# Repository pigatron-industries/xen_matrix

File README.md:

# Matrix Mixer

A Eurorack module 6x6 matrix mixer

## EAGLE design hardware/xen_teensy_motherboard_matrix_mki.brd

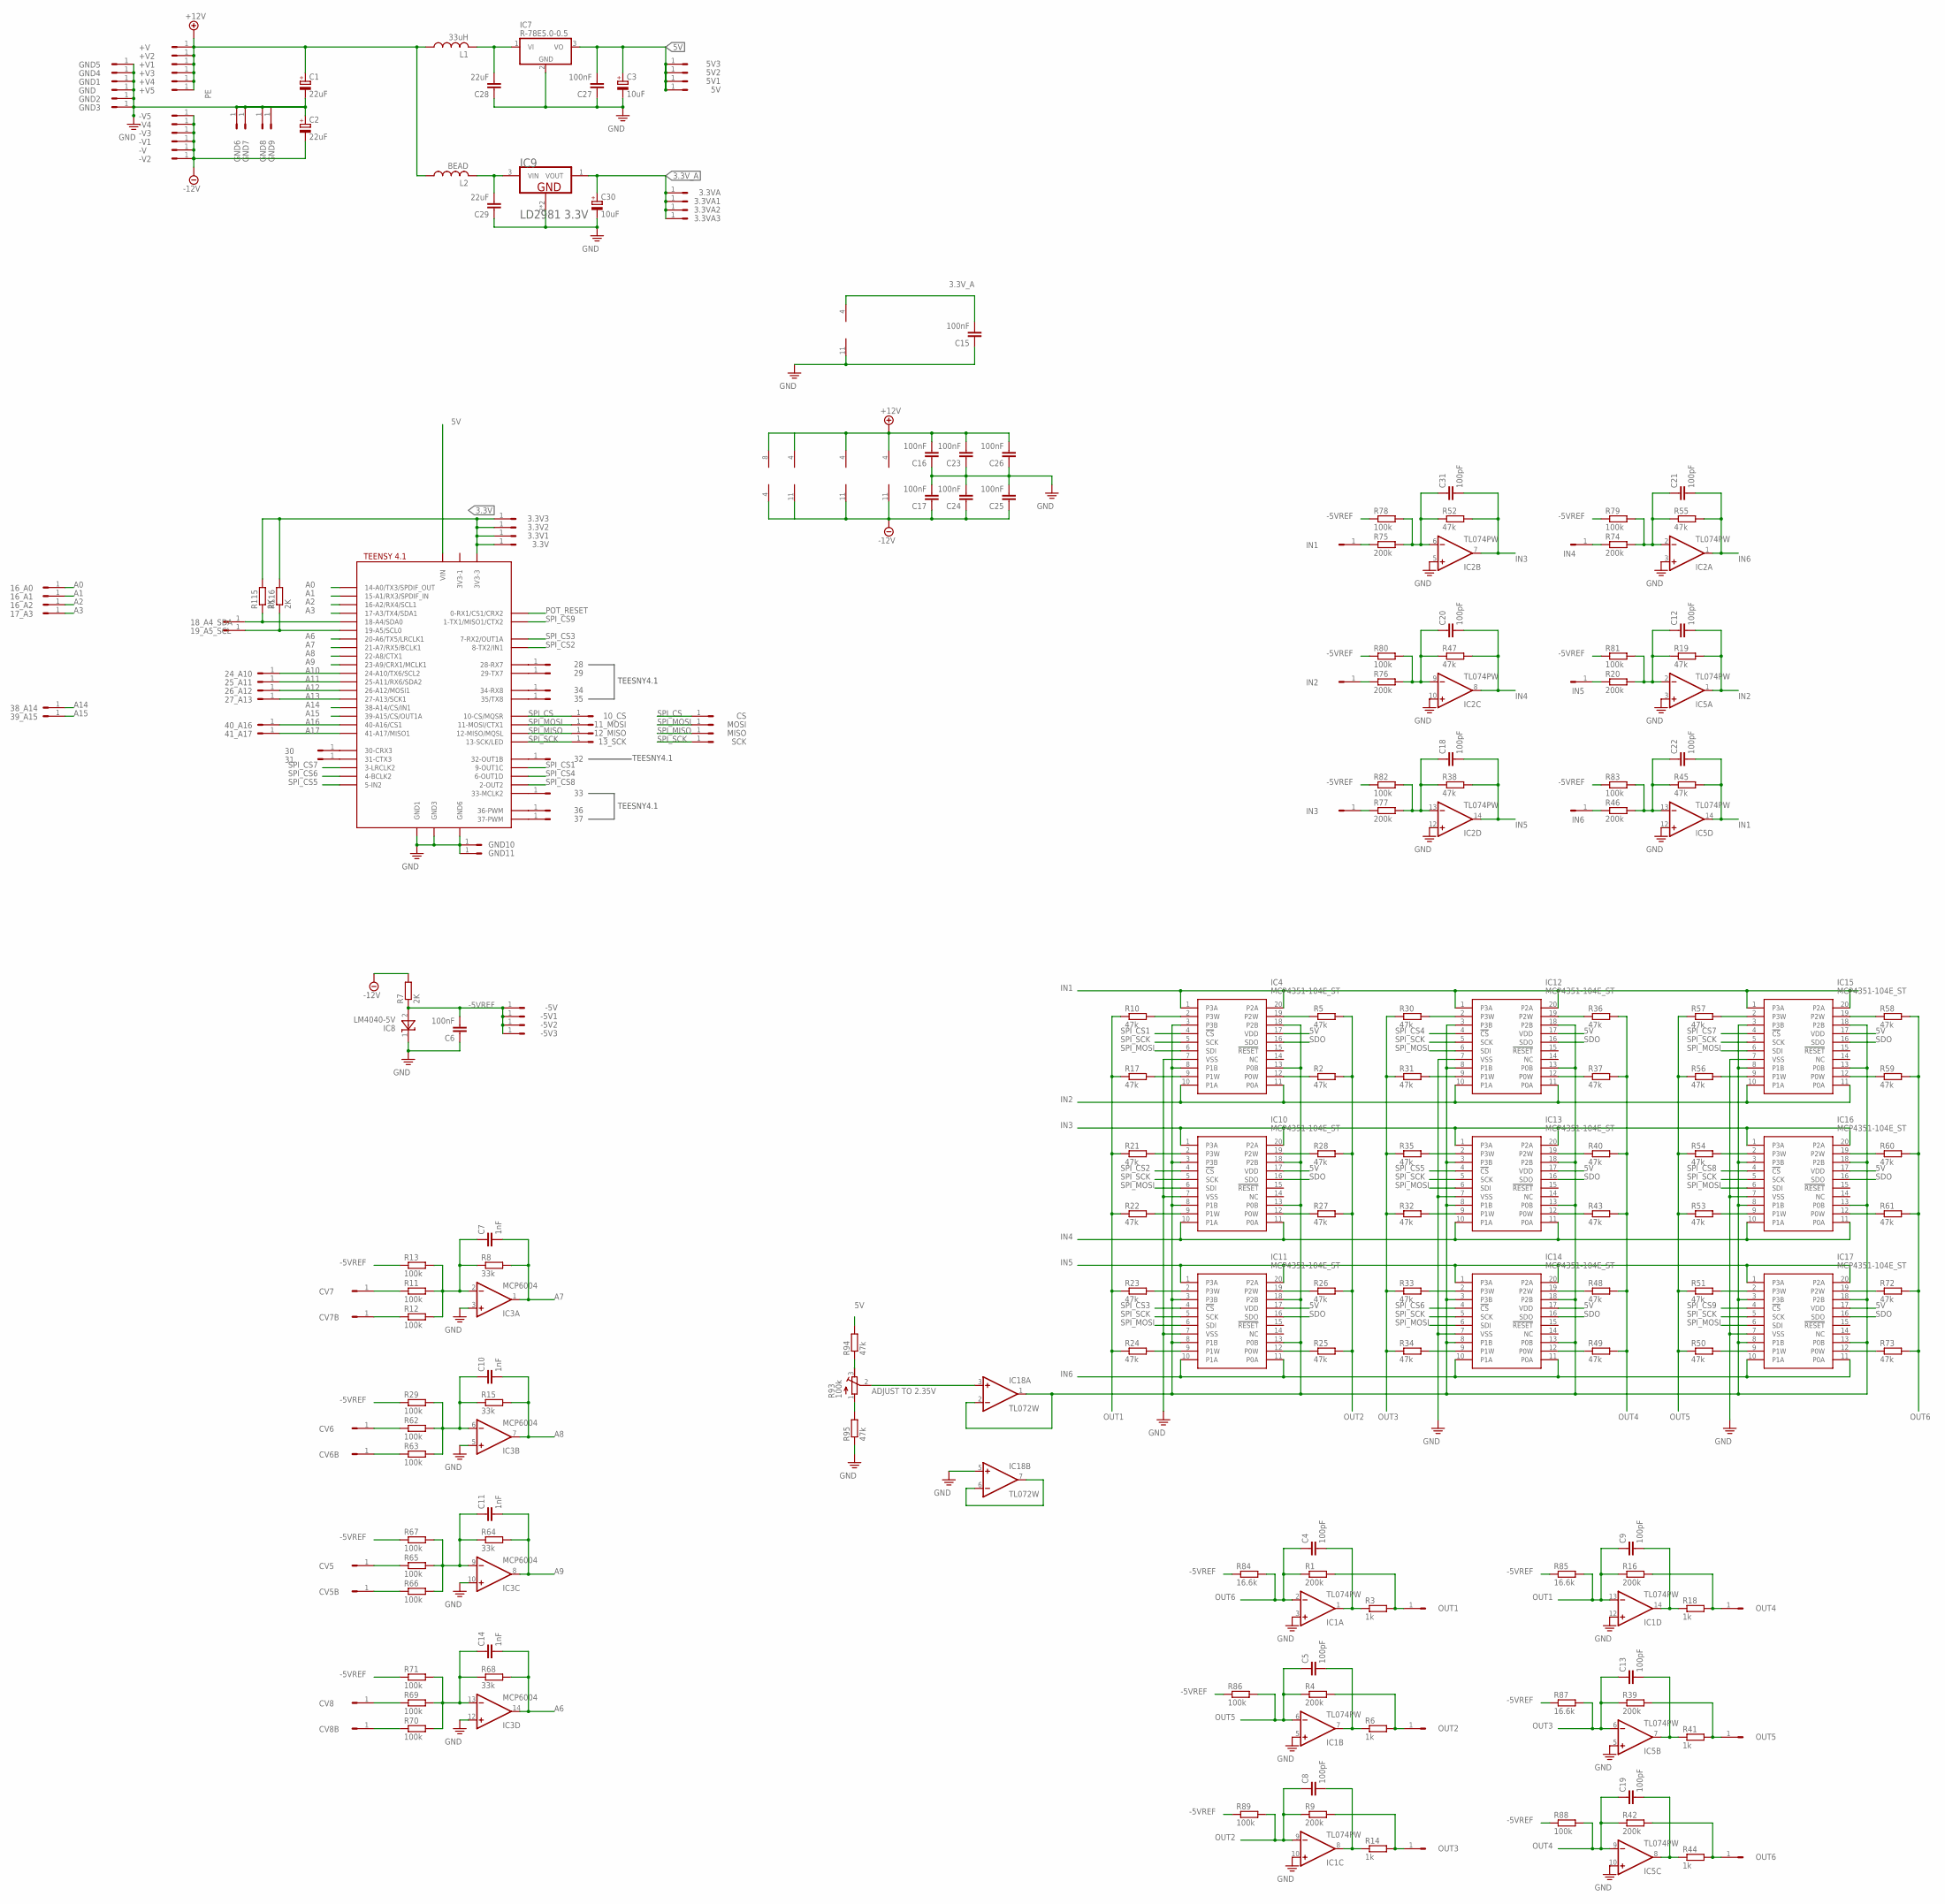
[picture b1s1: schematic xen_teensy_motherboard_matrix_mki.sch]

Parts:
3.3V, 3.3V1, 3.3V2, 3.3V3, 3.3VA, 3.3VA1, 3.3VA2, 3.3VA3, 5V, 5V1, 5V2, 5V3, 10_CS, 11_MOSI, 12_MISO, 13_SCK, 16_A0, 16_A1, 16_A2, 17_A3, 18_A4_SDA, 19_A5_SCL, 24_A10, 25_A11, 26_A12, 27_A13, 28, 29, 30, 31, 32, 33, 34, 35, 36, 37, 38_A14, 39_A15, 40_A16, 41_A17: HEADER/MALE/01
+V, +V1, +V2, +V3, +V4, +V5: HEADER/MALE/01
-5V, -5V1, -5V2, -5V3: HEADER/MALE/01
-V, -V1, -V2, -V3, -V4, -V5: HEADER/MALE/01
C1, C2: 22uF; SV-C
C3, C30: 10uF; SV-B
C4, C5, C8, C9, C12, C13, C18, C19, C20, C21, C22, C31: 100pF; C0603
C6, C15, C16, C17, C23, C24, C25, C26, C27: 100nF; C0603
C7, C10, C11, C14: 1nF; C0603
C28, C29: 22uF; C0805
CS: HEADER/MALE/01
CV5, CV5B, CV6, CV6B, CV7, CV7B, CV8, CV8B: HEADER/MALE/01
GND, GND1, GND2, GND3, GND4, GND5, GND6, GND7, GND8, GND9, GND10, GND11: HEADER/MALE/01
IC1, IC2, IC5: TL074PW; TSSOP14
IC3: MCP6004; TSSOP14
IC4, IC10, IC11, IC12, IC13, IC14, IC15, IC16, IC17: MCP4351-104E_ST; SOP65P640X120-20N
IC6: TEENSY41-OUTER; TENNSY41-OUTER
IC7: R-78E5.0-0.5; WE78
IC8: LM4040-5V; SOT-23
IC9: LD2981 3.3V; LD2981-SOT89
IC18: TL072W; TSSOP08
IN1, IN2, IN3, IN4, IN5, IN6: HEADER/MALE/01
L1: 33uH; L2012C
L2: BEAD; R0603
MISO: HEADER/MALE/01
MOSI: HEADER/MALE/01
OUT1, OUT2, OUT3, OUT4, OUT5, OUT6: HEADER/MALE/01
R1, R4, R9, R16, R20, R39, R42, R46, R74, R75, R76, R77: 200k; R0603
R2, R5, R10, R17, R19, R21, R22, R23, R24, R25, R26, R27, R28, R30, R31, R32, R33, R34, R35, R36, R37, R38, R40, R43, R45, R47, R48, R49, R50, R51, R52, R53, R54, R55, R56, R57, R58, R59, R60, R61, R72, R73, R94, R95: 47k; R0603
R3, R6, R14, R18, R41, R44: 1k; R0603
R7, R115, R116: 2K; R0603
R8, R15, R64, R68: 33k; R0603
R11, R12, R13, R29, R62, R63, R65, R66, R67, R69, R70, R71, R78, R79, R80, R81, R82, R83, R86, R88, R89: 100k; R0603
R84, R85, R87: 16.6k; R0603
R93: 100k; TRIMMER/64B
SCK: HEADER/MALE/01

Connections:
3.3V: 3.3V.1, 3.3V1.1, 3.3V2.1, 3.3V3.1, IC6.3V3-3, R115.2, R116.2
3.3V_A: 3.3VA.1, 3.3VA1.1, 3.3VA2.1, 3.3VA3.1, C15.2, C30.+, IC3.4 (V+), IC9.1 (VOUT)
5V: 5V.1, 5V1.1, 5V2.1, 5V3.1, C3.+, C27.2, IC4.17 (VDD), IC6.VIN, IC7.3 (VO), IC10.17 (VDD), IC11.17 (VDD), IC12.17 (VDD), IC13.17 (VDD), IC14.17 (VDD), IC15.17 (VDD), IC16.17 (VDD), IC17.17 (VDD), R94.2
+12V: +V.1, +V1.1, +V2.1, +V3.1, +V4.1, +V5.1, C1.+, C16.2, C23.2, C26.2, IC1.4 (V+), IC2.4 (V+), IC5.4 (V+), IC18.8 (V+), L1.1, L2.1
-5VREF: -5V.1, -5V1.1, -5V2.1, -5V3.1, C6.2, IC8.2 (A), R7.1, R13.1, R29.1, R67.1, R71.1, R78.1, R79.1, R80.1, R81.1, R82.1, R83.1, R84.1, R85.1, R86.1, R87.1, R88.1, R89.1
-12V: -V.1, -V1.1, -V2.1, -V3.1, -V4.1, -V5.1, C2.-, C17.1, C24.1, C25.1, IC1.11 (V-), IC2.11 (V-), IC5.11 (V-), IC18.4 (V-), R7.2
A0: 16_A0.1, IC6.14-A0/TX3/SPDIF_OUT
A1: 16_A1.1, IC6.15-A1/RX3/SPDIF_IN
A2: 16_A2.1, IC6.16-A2/RX4/SCL1
A3: 17_A3.1, IC6.17-A3/TX4/SDA1
A5: 19_A5_SCL.1, IC6.19-A5/SCL0, R116.1
A6: C14.2, IC3.14 (OUT), IC6.20-A6/TX5/LRCLK1, R68.2
A7: C7.2, IC3.1 (OUT), IC6.21-A7/RX5/BCLK1, R8.2
A8: C10.2, IC3.7 (OUT), IC6.22-A8/CTX1, R15.2
A9: C11.2, IC3.8 (OUT), IC6.23-A9/CRX1/MCLK1, R64.2
A10: 24_A10.1, IC6.24-A10/TX6/SCL2
A11: 25_A11.1, IC6.25-A11/RX6/SDA2
A12: 26_A12.1, IC6.26-A12/MOSI1
A13: 27_A13.1, IC6.27-A13/SCK1
A14: 38_A14.1, IC6.38-A14/CS/IN1
A15: 39_A15.1, IC6.39-A15/CS/OUT1A
A16: 40_A16.1, IC6.40-A16/CS1
A17: 41_A17.1, IC6.41-A17/MISO1
DAC1: IN6.1, R46.1
DAC2: IN5.1, R20.1
IN1: C22.2, IC4.1 (P3A), IC4.20 (P2A), IC5.14 (OUT), IC12.1 (P3A), IC12.20 (P2A), IC15.1 (P3A), IC15.20 (P2A), R45.2
IN2: C12.2, IC4.10 (P1A), IC4.11 (P0A), IC5.1 (OUT), IC12.10 (P1A), IC12.11 (P0A), IC15.10 (P1A), IC15.11 (P0A), R19.2
IN3: C31.2, IC2.7 (OUT), IC10.1 (P3A), IC10.20 (P2A), IC13.1 (P3A), IC13.20 (P2A), IC16.1 (P3A), IC16.20 (P2A), R52.2
IN4: C20.2, IC2.8 (OUT), IC10.10 (P1A), IC10.11 (P0A), IC13.10 (P1A), IC13.11 (P0A), IC16.10 (P1A), IC16.11 (P0A), R47.2
IN5: C18.2, IC2.14 (OUT), IC11.1 (P3A), IC11.20 (P2A), IC14.1 (P3A), IC14.20 (P2A), IC17.1 (P3A), IC17.20 (P2A), R38.2
IN6: C21.2, IC2.1 (OUT), IC11.10 (P1A), IC11.11 (P0A), IC14.10 (P1A), IC14.11 (P0A), IC17.10 (P1A), IC17.11 (P0A), R55.2
unnamed: IC4.2 (P3W), R10.2
unnamed: C18.1, IC2.13 (-IN), R38.1, R77.2, R82.2
unnamed: C4.2, IC1.1 (OUT), R3.1
unnamed: OUT1.1, R1.2, R3.2
unnamed: IC4.3 (P3B), IC4.8 (P1B), IC4.13 (P0B), IC4.18 (P2B), IC10.3 (P3B), IC10.8 (P1B), IC10.13 (P0B), IC10.18 (P2B), IC11.3 (P3B), IC11.8 (P1B), IC11.13 (P0B), IC11.18 (P2B), IC12.3 (P3B), IC12.8 (P1B), IC12.13 (P0B), IC12.18 (P2B), IC13.3 (P3B), IC13.8 (P1B), IC13.13 (P0B), IC13.18 (P2B), IC14.3 (P3B), IC14.8 (P1B), IC14.13 (P0B), IC14.18 (P2B), IC15.3 (P3B), IC15.8 (P1B), IC15.13 (P0B), IC15.18 (P2B), IC16.3 (P3B), IC16.8 (P1B), IC16.13 (P0B), IC16.18 (P2B), IC17.3 (P3B), IC17.8 (P1B), IC17.13 (P0B), IC17.18 (P2B), IC18.1 (OUT), IC18.2 (-IN)
unnamed: C5.2, IC1.7 (OUT), R6.1
unnamed: OUT2.1, R4.2, R6.2
unnamed: C7.1, IC3.2 (-IN), R8.1, R11.2, R12.2, R13.2
unnamed: IC18.3 (+IN), R93.2 (S)
unnamed: C8.2, IC1.8 (OUT), R14.1
unnamed: OUT3.1, R9.2, R14.2
unnamed: C20.1, IC2.9 (-IN), R47.1, R76.2, R80.2
unnamed: CV7B.1, R12.1
unnamed: CV7.1, R11.1
unnamed: C9.2, IC1.14 (OUT), R18.1
unnamed: C10.1, IC3.6 (-IN), R15.1, R29.2, R62.2, R63.2
unnamed: OUT4.1, R16.2, R18.2
unnamed: CV6.1, R62.1
unnamed: CV6B.1, R63.1
unnamed: C12.1, IC5.2 (-IN), R19.1, R20.2, R81.2
unnamed: IC18.6 (-IN), IC18.7 (OUT)
unnamed: IC4.9 (P1W), R17.2
unnamed: IC10.2 (P3W), R21.2
unnamed: IC10.9 (P1W), R22.2
unnamed: IC11.2 (P3W), R23.2
unnamed: IC11.9 (P1W), R24.2
unnamed: C31.1, IC2.6 (-IN), R52.1, R75.2, R78.2
unnamed: IC11.12 (P0W), R25.1
unnamed: IC11.19 (P2W), R26.1
unnamed: IC10.12 (P0W), R27.1
unnamed: IC10.19 (P2W), R28.1
unnamed: C13.2, IC5.7 (OUT), R41.1
unnamed: IC4.12 (P0W), R2.1
unnamed: IC4.19 (P2W), R5.1
unnamed: IC12.2 (P3W), R30.2
unnamed: IC12.9 (P1W), R31.2
unnamed: IC13.2 (P3W), R35.2
unnamed: IC13.9 (P1W), R32.2
unnamed: IC14.2 (P3W), R33.2
unnamed: IC14.9 (P1W), R34.2
unnamed: OUT5.1, R39.2, R41.2
unnamed: R93.1 (E), R95.2
unnamed: C19.2, IC5.8 (OUT), R44.1
unnamed: 18_A4_SDA.1, IC6.18-A4/SDA0, R115.1
unnamed: IC14.12 (P0W), R49.1
unnamed: OUT6.1, R42.2, R44.2
unnamed: C22.1, IC5.13 (-IN), R45.1, R46.2, R83.2
unnamed: R93.3 (A), R94.1
unnamed: C21.1, IC2.2 (-IN), R55.1, R74.2, R79.2
unnamed: C28.2, IC7.1 (VI), L1.2
unnamed: IC14.19 (P2W), R48.1
unnamed: IC13.12 (P0W), R43.1
unnamed: IC13.19 (P2W), R40.1
unnamed: IC12.12 (P0W), R37.1
unnamed: IC12.19 (P2W), R36.1
unnamed: C14.1, IC3.13 (-IN), R68.1, R69.2, R70.2, R71.2
unnamed: IC15.2 (P3W), R57.2
unnamed: IC15.9 (P1W), R56.2
unnamed: CV8.1, R69.1
unnamed: IC16.2 (P3W), R54.2
unnamed: IC16.9 (P1W), R53.2
unnamed: IC17.2 (P3W), R51.2
unnamed: IC17.9 (P1W), R50.2
unnamed: IC17.12 (P0W), R73.1
unnamed: IC17.19 (P2W), R72.1
unnamed: IC16.12 (P0W), R61.1
unnamed: CV8B.1, R70.1
unnamed: CV5B.1, R66.1
unnamed: CV5.1, R65.1
unnamed: C11.1, IC3.9 (-IN), R64.1, R65.2, R66.2, R67.2
unnamed: C29.2, IC9.3 (VIN), L2.2
unnamed: IC16.19 (P2W), R60.1
unnamed: IC15.12 (P0W), R59.1
unnamed: IC15.19 (P2W), R58.1
unnamed: IN1.1, R75.1
unnamed: IN2.1, R76.1
unnamed: IN3.1, R77.1
unnamed: IN4.1, R74.1
unnamed: 28.1, IC6.28-RX7
unnamed: 29.1, IC6.29-TX7
unnamed: 30.1, IC6.30-CRX3
unnamed: 31.1, IC6.31-CTX3
unnamed: 32.1, IC6.32-OUT1B
unnamed: 34.1, IC6.34-RX8
unnamed: 35.1, IC6.35-TX8 (35/TX8)
unnamed: 33.1, IC6.33-MCLK2
unnamed: 36.1, IC6.36-PWM
unnamed: 37.1, IC6.37-PWM
OUT1: C9.1, IC1.13 (-IN), R10.1, R16.1, R17.1, R21.1, R22.1, R23.1, R24.1, R85.2
OUT2: C8.1, IC1.9 (-IN), R2.2, R5.2, R9.1, R25.2, R26.2, R27.2, R28.2, R89.2
OUT3: C13.1, IC5.6 (-IN), R30.1, R31.1, R32.1, R33.1, R34.1, R35.1, R39.1, R87.2
OUT4: C19.1, IC5.9 (-IN), R36.2, R37.2, R40.2, R42.1, R43.2, R48.2, R49.2, R88.2
OUT5: C5.1, IC1.6 (-IN), R4.1, R50.1, R51.1, R53.1, R54.1, R56.1, R57.1, R86.2
OUT6: C4.1, IC1.2 (-IN), R1.1, R58.2, R59.2, R60.2, R61.2, R72.2, R73.2, R84.2
PE: C1.-, C2.+, C3.-, C6.1, C15.1, C16.1, C17.2, C23.1, C24.2, C25.2, C26.1, C27.1, C28.1, C29.1, C30.-, GND.1, GND1.1, GND2.1, GND3.1, GND4.1, GND5.1, GND6.1, GND7.1, GND8.1, GND9.1, GND10.1, GND11.1, IC1.3 (+IN), IC1.5 (+IN), IC1.10 (+IN), IC1.12 (+IN), IC2.3 (+IN), IC2.5 (+IN), IC2.10 (+IN), IC2.12 (+IN), IC3.3 (+IN), IC3.5 (+IN), IC3.10 (+IN), IC3.11 (V-), IC3.12 (+IN), IC4.7 (VSS), IC5.3 (+IN), IC5.5 (+IN), IC5.10 (+IN), IC5.12 (+IN), IC6.GND1, IC6.GND3, IC6.GND6, IC7.2 (GND), IC8.1 (C), IC9.2 (GND), IC9.2-2 (GND), IC10.7 (VSS), IC11.7 (VSS), IC12.7 (VSS), IC13.7 (VSS), IC14.7 (VSS), IC15.7 (VSS), IC16.7 (VSS), IC17.7 (VSS), IC18.5 (+IN), R95.1
POT_RESET: IC6.0-RX1/CS1/CRX2
SDO: IC4.16 (SDO), IC10.16 (SDO), IC11.16 (SDO), IC12.16 (SDO), IC13.16 (SDO), IC14.16 (SDO), IC15.16 (SDO), IC16.16 (SDO), IC17.16 (SDO)
SPI_CS: 10_CS.1, CS.1, IC6.10-CS\MQSR (10-CS/MQSR)
SPI_CS1: IC4.4 (!CS), IC6.9-OUT1C
SPI_CS2: IC6.8-TX2/IN1, IC10.4 (!CS)
SPI_CS3: IC6.7-RX2/OUT1A, IC11.4 (!CS)
SPI_CS4: IC6.6-OUT1D, IC12.4 (!CS)
SPI_CS5: IC6.5-IN2, IC13.4 (!CS)
SPI_CS6: IC6.4-BCLK2, IC14.4 (!CS)
SPI_CS7: IC6.3-LRCLK2, IC15.4 (!CS)
SPI_CS8: IC6.2-OUT2, IC16.4 (!CS)
SPI_CS9: IC6.1-TX1/MISO1/CTX2, IC17.4 (!CS)
SPI_MISO: 12_MISO.1, IC6.12-MISO/MQSL, MISO.1
SPI_MOSI: 11_MOSI.1, IC4.6 (SDI), IC6.11-MOSI/CTX1, IC10.6 (SDI), IC11.6 (SDI), IC12.6 (SDI), IC13.6 (SDI), IC14.6 (SDI), IC15.6 (SDI), IC16.6 (SDI), IC17.6 (SDI), MOSI.1
SPI_SCK: 13_SCK.1, IC4.5 (SCK), IC6.13-SCK/LED, IC10.5 (SCK), IC11.5 (SCK), IC12.5 (SCK), IC13.5 (SCK), IC14.5 (SCK), IC15.5 (SCK), IC16.5 (SCK), IC17.5 (SCK), SCK.1

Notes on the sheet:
TEESNY4.1
ADJUST TO 2.35V

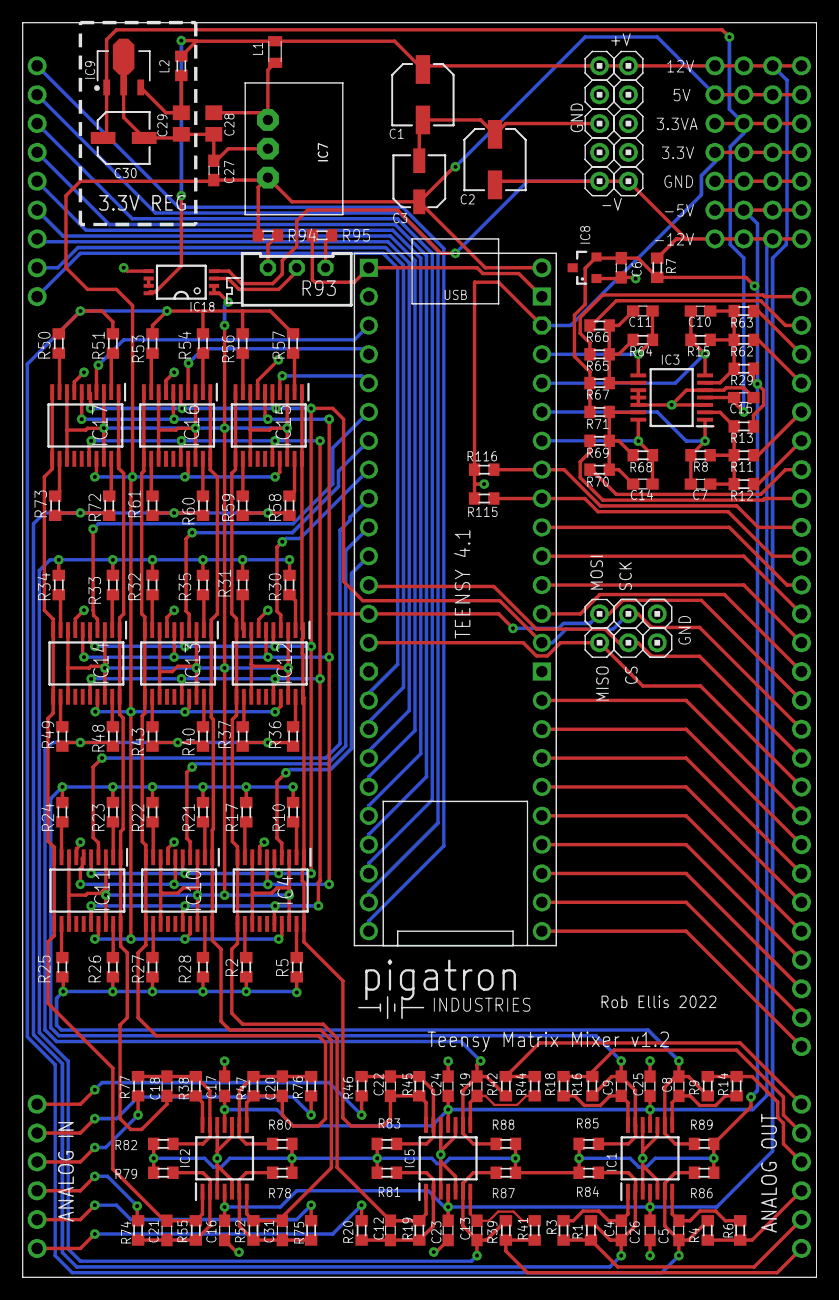
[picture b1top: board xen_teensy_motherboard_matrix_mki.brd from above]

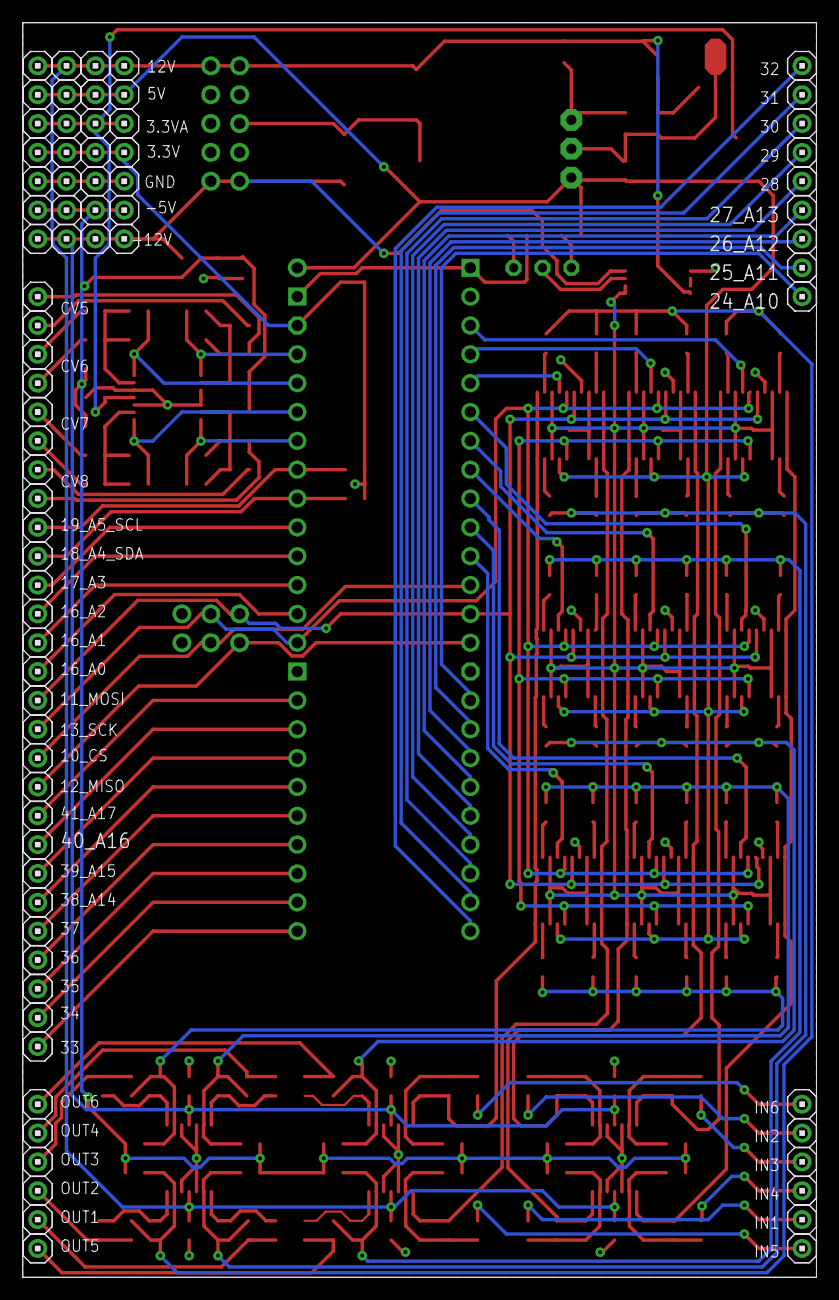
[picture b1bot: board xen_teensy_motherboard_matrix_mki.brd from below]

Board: 2 copper layers, 69.9 x 110.5 mm, 238 parts (76 on the bottom side), 140 nets.

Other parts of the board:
U$1: PIGATRON-LOGO

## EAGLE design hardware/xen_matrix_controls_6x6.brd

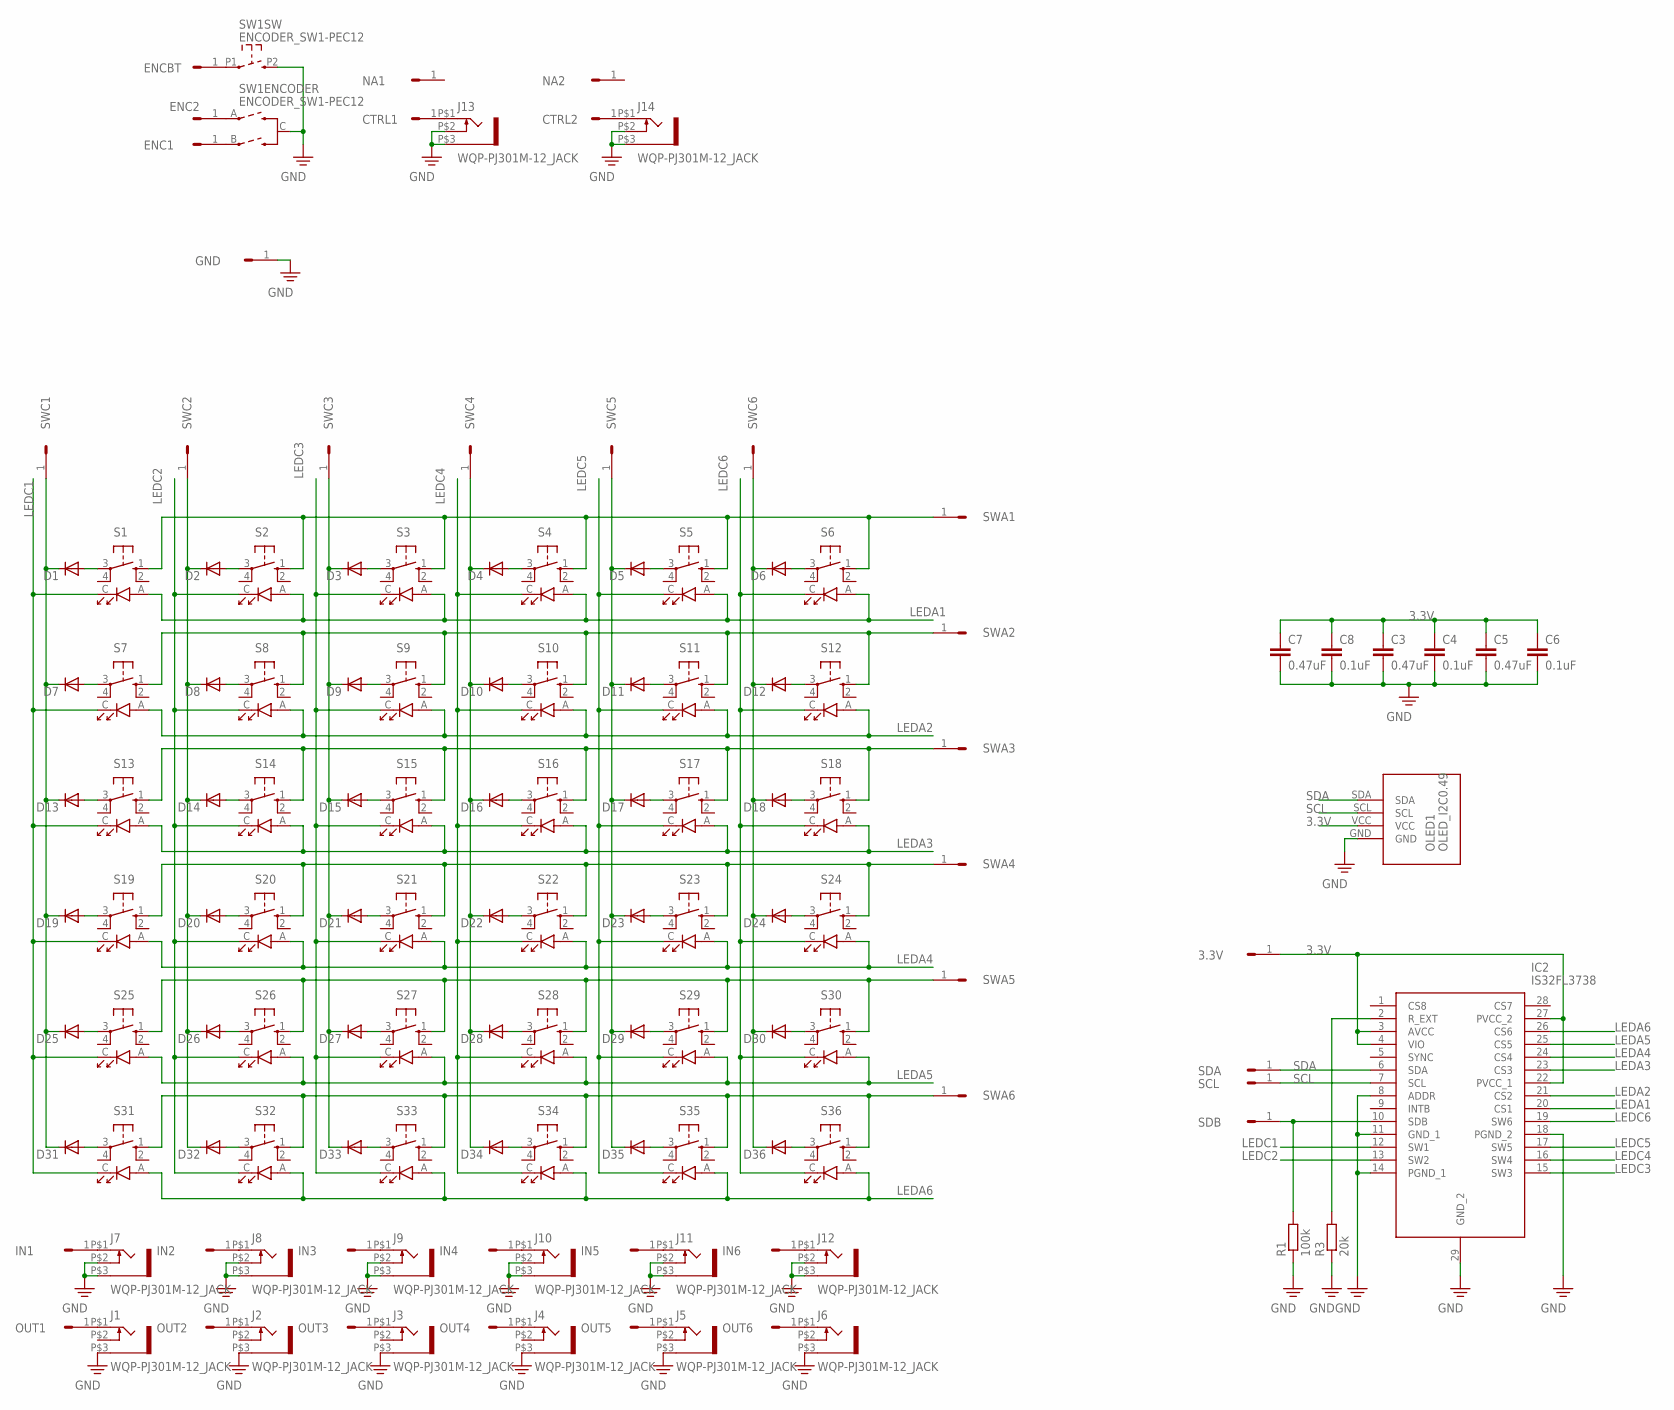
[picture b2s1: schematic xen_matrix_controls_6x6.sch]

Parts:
3.3V: HEADER/MALE/01
C3, C5, C7: 0.47uF; C0603
C4, C6, C8: 0.1uF; C0603
CTRL1, CTRL2: HEADER/MALE/01
D1, D2, D3, D4, D5, D6, D7, D8, D9, D10, D11, D12, D13, D14, D15, D16, D17, D18, D19, D20, D21, D22, D23, D24, D25, D26, D27, D28, D29, D30, D31, D32, D33, D34, D35, D36: 1N4148SOD-123; SOD-123
ENC1, ENC2: HEADER/MALE/01
ENCBT: HEADER/MALE/01
GND: HEADER/MALE/01
IC2: IS32FL3738; TSSOP29
IN1, IN2, IN3, IN4, IN5, IN6: HEADER/MALE/01
J1, J2, J3, J4, J5, J6, J7, J8, J9, J10, J11, J12, J13, J14: WQP-PJ301M-12_JACK
NA1, NA2: HEADER/MALE/01
OLED1: OLED_I2C0.49; OLEDM0.49
OUT1, OUT2, OUT3, OUT4, OUT5, OUT6: HEADER/MALE/01
R1: 100k; R0603
R3: 20k; R0603
S1, S2, S3, S4, S5, S6, S7, S8, S9, S10, S11, S12, S13, S14, S15, S16, S17, S18, S19, S20, S21, S22, S23, S24, S25, S26, S27, S28, S29, S30, S31, S32, S33, S34, S35, S36: SW-LEDTHONK; SW-PUSH-TACT-LED-THONK
SCL: HEADER/MALE/01
SDA: HEADER/MALE/01
SDB: HEADER/MALE/01
SW1: ENCODER_SW1-PEC12; PEC12_INCREMENTAL_ENCODER
SWA1, SWA2, SWA3, SWA4, SWA5, SWA6: HEADER/MALE/01
SWC1, SWC2, SWC3, SWC4, SWC5, SWC6: HEADER/MALE/01

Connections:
3.3V: 3.3V.1, C3.1, C4.1, C5.1, C6.1, C7.1, C8.1, IC2.3 (AVCC), IC2.4 (VIO), IC2.22 (PVCC_1), IC2.27 (PVCC_2), OLED1.VCC
LEDA1: IC2.20 (CS1), S1.A, S2.A, S3.A, S4.A, S5.A, S6.A
LEDA2: IC2.21 (CS2), S7.A, S8.A, S9.A, S10.A, S11.A, S12.A
LEDA3: IC2.23 (CS3), S13.A, S14.A, S15.A, S16.A, S17.A, S18.A
LEDA4: IC2.24 (CS4), S19.A, S20.A, S21.A, S22.A, S23.A, S24.A
LEDA5: IC2.25 (CS5), S25.A, S26.A, S27.A, S28.A, S29.A, S30.A
LEDA6: IC2.26 (CS6), S31.A, S32.A, S33.A, S34.A, S35.A, S36.A
LEDC1: IC2.12 (SW1), S1.C, S7.C, S13.C, S19.C, S25.C, S31.C
LEDC2: IC2.13 (SW2), S2.C, S8.C, S14.C, S20.C, S26.C, S32.C
LEDC3: IC2.15 (SW3), S3.C, S9.C, S15.C, S21.C, S27.C, S33.C
LEDC4: IC2.16 (SW4), S4.C, S10.C, S16.C, S22.C, S28.C, S34.C
LEDC5: IC2.17 (SW5), S5.C, S11.C, S17.C, S23.C, S29.C, S35.C
LEDC6: IC2.19 (SW6), S6.C, S12.C, S18.C, S24.C, S30.C, S36.C
unnamed: IC2.10 (SDB), R1.2, SDB.1
unnamed: IC2.2 (R_EXT), R3.2
unnamed: S25.1 (S), S26.1 (S), S27.1 (S), S28.1 (S), S29.1 (S), S30.1 (S), SWA5.1
unnamed: S1.1 (S), S2.1 (S), S3.1 (S), S4.1 (S), S5.1 (S), S6.1 (S), SWA1.1
unnamed: D1.A, S1.3
unnamed: S7.1 (S), S8.1 (S), S9.1 (S), S10.1 (S), S11.1 (S), S12.1 (S), SWA2.1
unnamed: D4.A, S4.3
unnamed: D5.A, S5.3
unnamed: S13.1 (S), S14.1 (S), S15.1 (S), S16.1 (S), S17.1 (S), S18.1 (S), SWA3.1
unnamed: S19.1 (S), S20.1 (S), S21.1 (S), S22.1 (S), S23.1 (S), S24.1 (S), SWA4.1
unnamed: D6.A, S6.3
unnamed: S31.1 (S), S32.1 (S), S33.1 (S), S34.1 (S), S35.1 (S), S36.1 (S), SWA6.1
unnamed: D7.A, S7.3
unnamed: D8.A, S8.3
unnamed: D9.A, S9.3
unnamed: D10.A, S10.3
unnamed: D11.A, S11.3
unnamed: D12.A, S12.3
unnamed: D13.A, S13.3
unnamed: D14.A, S14.3
unnamed: D15.A, S15.3
unnamed: D16.A, S16.3
unnamed: D17.A, S17.3
unnamed: D18.A, S18.3
unnamed: D19.A, S19.3
unnamed: D20.A, S20.3
unnamed: D21.A, S21.3
unnamed: D22.A, S22.3
unnamed: D23.A, S23.3
unnamed: D24.A, S24.3
unnamed: D25.A, S25.3
unnamed: D26.A, S26.3
unnamed: D27.A, S27.3
unnamed: D28.A, S28.3
unnamed: D29.A, S29.3
unnamed: D30.A, S30.3
unnamed: D31.A, S31.3
unnamed: D32.A, S32.3
unnamed: D33.A, S33.3
unnamed: D34.A, S34.3
unnamed: D35.A, S35.3
unnamed: D36.A, S36.3
unnamed: D2.A, S2.3
unnamed: D3.A, S3.3
unnamed: D1.C, D7.C, D13.C, D19.C, D25.C, D31.C, SWC1.1
unnamed: D2.C, D8.C, D14.C, D20.C, D26.C, D32.C, SWC2.1
unnamed: D3.C, D9.C, D15.C, D21.C, D27.C, D33.C, SWC3.1
unnamed: D4.C, D10.C, D16.C, D22.C, D28.C, D34.C, SWC4.1
unnamed: D5.C, D11.C, D17.C, D23.C, D29.C, D35.C, SWC5.1
unnamed: D6.C, D12.C, D18.C, D24.C, D30.C, D36.C, SWC6.1
unnamed: J2.P$1 (2), OUT2.1
unnamed: J1.P$1 (2), OUT1.1
unnamed: J3.P$1 (2), OUT3.1
unnamed: J4.P$1 (2), OUT4.1
unnamed: J5.P$1 (2), OUT5.1
unnamed: J6.P$1 (2), OUT6.1
unnamed: ENC2.1, SW1.A
unnamed: IN1.1, J7.P$1 (2)
unnamed: IN2.1, J8.P$1 (2)
unnamed: IN3.1, J9.P$1 (2)
unnamed: IN4.1, J10.P$1 (2)
unnamed: IN5.1, J11.P$1 (2)
unnamed: IN6.1, J12.P$1 (2)
unnamed: CTRL1.1, J13.P$1 (2)
unnamed: CTRL2.1, J14.P$1 (2)
unnamed: ENC1.1, SW1.B
unnamed: ENCBT.1, SW1.P1 (1)
PE: C3.2, C4.2, C5.2, C6.2, C7.2, C8.2, GND.1, IC2.8 (ADDR), IC2.11 (GND_1), IC2.14 (PGND_1), IC2.18 (PGND_2), IC2.29 (GND_2), J1.P$3 (1), J2.P$3 (1), J3.P$3 (1), J4.P$3 (1), J5.P$3 (1), J6.P$3 (1), J7.P$2 (3), J7.P$3 (1), J8.P$2 (3), J8.P$3 (1), J9.P$2 (3), J9.P$3 (1), J10.P$2 (3), J10.P$3 (1), J11.P$2 (3), J11.P$3 (1), J12.P$2 (3), J12.P$3 (1), J13.P$2 (3), J13.P$3 (1), J14.P$2 (3), J14.P$3 (1), OLED1.GND, R1.1, R3.1, SW1.C, SW1.P2 (2)
SCL: IC2.7 (SCL), OLED1.SCL, SCL.1
SDA: IC2.6 (SDA), OLED1.SDA, SDA.1

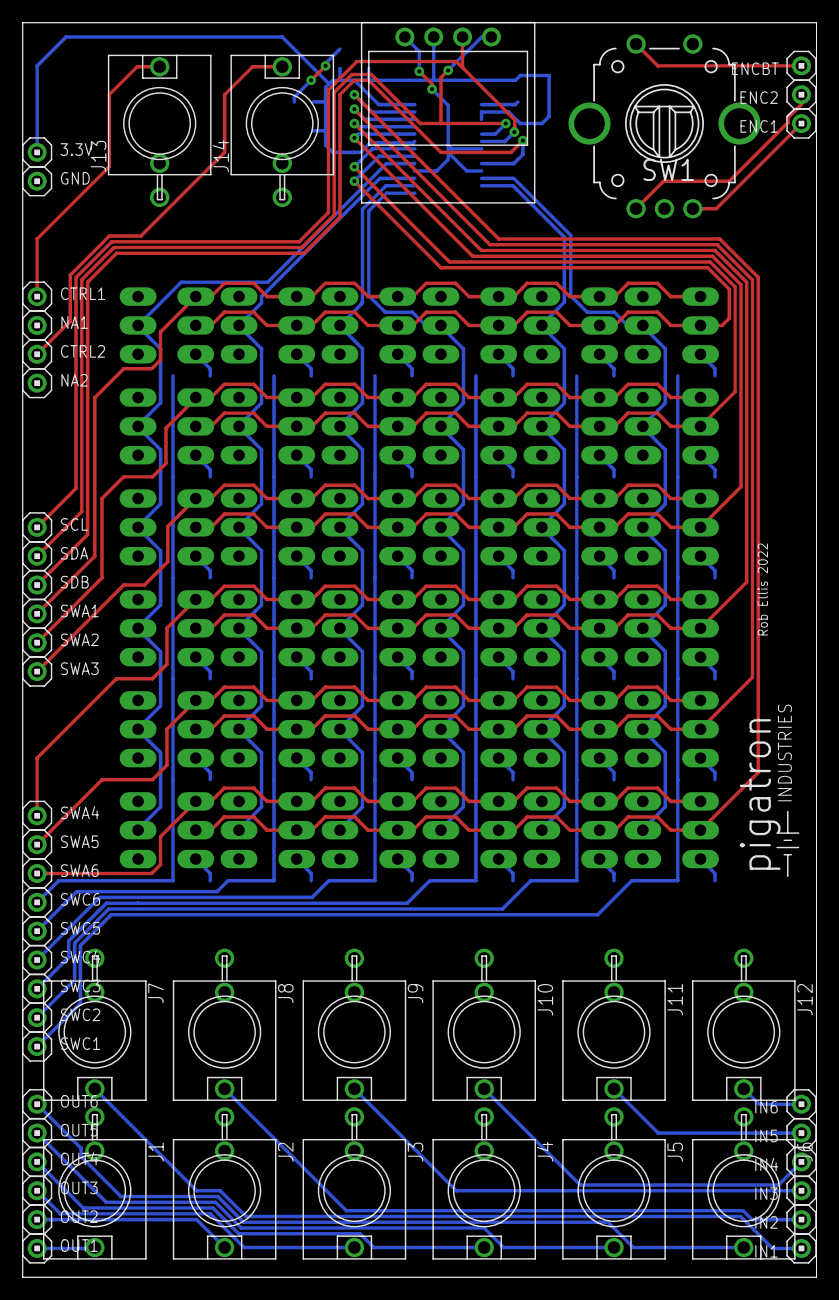
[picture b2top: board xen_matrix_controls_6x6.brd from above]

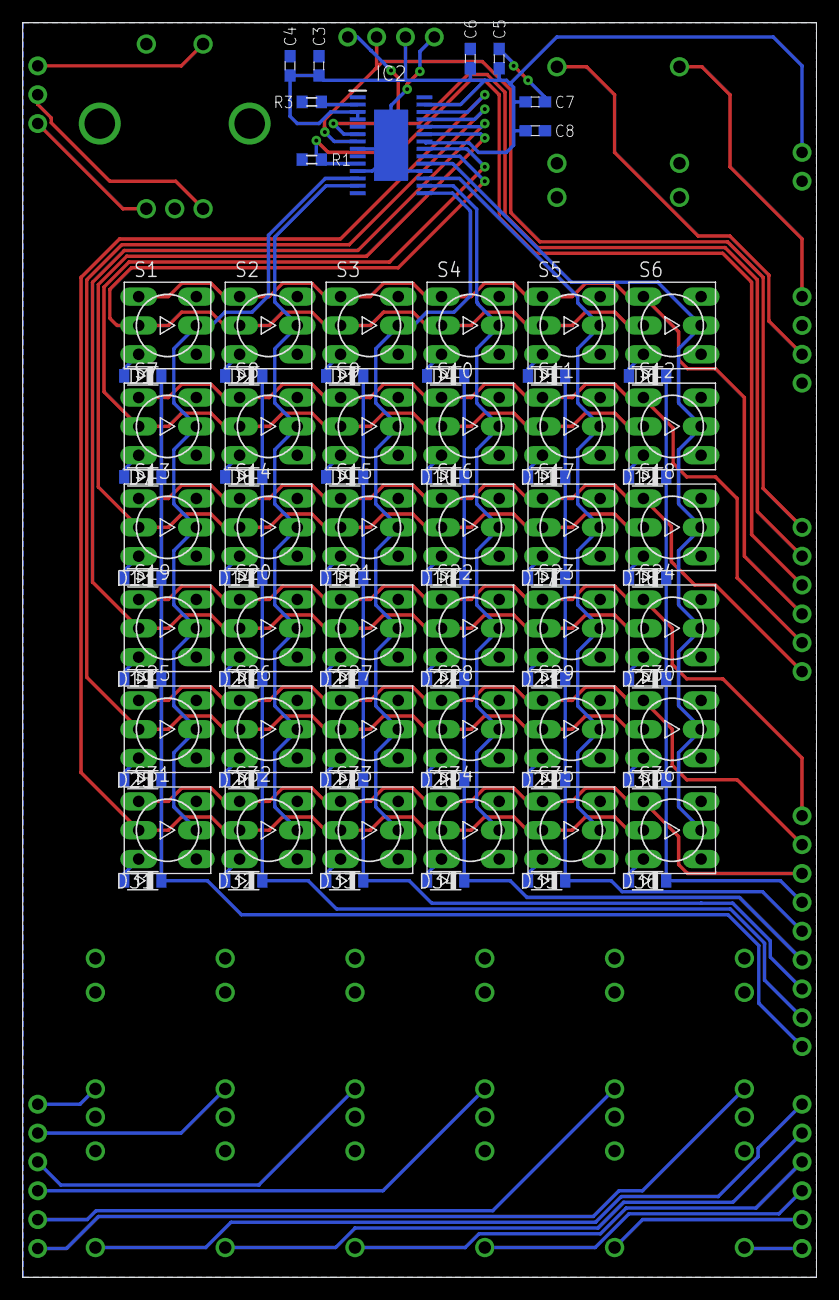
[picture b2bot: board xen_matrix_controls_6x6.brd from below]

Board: 2 copper layers, 69.9 x 110.5 mm, 134 parts (81 on the bottom side), 83 nets.

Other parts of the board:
U$1: PIGATRON-LOGO

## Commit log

2022-12-03 .gitignore
2022-12-03 Added skeleton framework code
2022-12-03 call to main controller
2022-12-03 Add hardware pin defs
2022-12-25 Code for matrix leds, pots and key matrix
2023-02-06 add offset to input and output voltages
2023-07-19 add oled display + router mode
2023-07-19 use parameterized controller from lib
2023-07-20 implement bank selection
2023-08-13 add parameters to display
2023-08-14 save matrix states to eeprom
2023-08-17 detect multiple key events
2023-08-17 save matrix after toggling value
2023-10-28 buffer calibration voltage
2024-01-14 fix key handling
